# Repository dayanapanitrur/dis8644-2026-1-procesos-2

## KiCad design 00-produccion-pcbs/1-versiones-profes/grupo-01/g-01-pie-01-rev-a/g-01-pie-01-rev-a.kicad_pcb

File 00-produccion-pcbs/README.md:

# produccion-pcbs

jornada maratónica sábado 06 junio 2026

equipo docente toma todos los proyectos de kicad entregados el día anterior, de proyecto-02, y con eso edita, revisa, y envía a producción.

hay 6 grupos de trabajo con una temática en particular, cada grupo realizó 2 esquemáticos con sus respectivas placas, en varias versiones que subieron a la carpeta 00-proyecto-02.

a continuación los apuntes de las distintas revisiones hechas de estos proyectos, para prepararlos para su producción física.

en este repo creamos 3 carpetas:

- 0-versiones-estudiantes: archivos de kicad con las versiones más recientes de proyectos de estudiantes
- 1-versiones-profes: archivos de kicad con las versiones revisadas y realizadas por equipo docentes
- 2-archivos-produccion: gerbers de producción, etiquetados como revA.

## grupo-01: piezos

- benjaminalvarez21
- Anaysval
- chknngttts
- ryukivol
- nicolasvaldesgreve

### g-01-pie-01-rev-a

- cambiamos tamaño r15
- cambiamos conector de entrada
- cambiamos nomenclatura de "100 u" a "100u"
- cambiamos huella de transistor Q1, porque era la equivocada

### g-01-pie-02-rev-a

- no fue enviado a producción porque no tenemos garantía de que funcionara según lo visto en protoboard.

## grupo-02: secuenciadores

- isidoraalvarez
- tomascatri
- dayanapanitrur
- Estrabismx
- angel-udp

### g-02-sec-01-rev-a

en esquemático:

- agregamos resistor de clock in a ground, para pulldown.
- agregamos resistor entre 4040 Q0 patita 9 y salida
- agregamos resistor a cada salida de jack switch.
- cambiamos huellas de transistores a versión inline_wide para que tengan más espacio
- agregados mounting hole faltantes

en pcb:

- actualizamos conectores jack a la huella de la biblioteca, para poder rutear bien los nuevos resistores y no perdernos.

### g-02-sec-02-rev-a

en esquemático:

- agregamos también resistores de protección en entradas y salidas.
- agregados mounting hole faltantes

en pcb:

- actualizamos conectores jack a la huella de la biblioteca, para poder rutear bien los nuevos resistores y no perdernos.

## grupo-03: osciladores 1

- vanessagarciaM
- antoloch
- ccarlabelenn
- arielorozco024
- Narelyriquelme

## grupo-04: osciladores 2

- antokiaraa
- santiagocifuvelez
- paulafuentesm
- kristelagj
- catalinaoyanedel
- yairaruiz

## grupo-05: filtros

- antoniaamc
- Catabalboa
- sebastianguevaralarotta
- CatalinaJeria
- Luisaatoro9

### g-05-fil-01-rev-a

- error grave en la nomenclatura de los proyectos: el 01 en su README dicen que es el activo, pero en Kicad es el pasivo
- cambiamos C1 por condensador no polarizado
- conectamos patita del medio de potenciómetro
- confusión en los tamaños de los condensadores C4 y C5
- los tamaños de las pistas usados no fueron los indicados en clases ni en estandarización
- faltó el paso de agregar tierra a la placa, no está hecho

### g-05-fil-02-rev-a

- error grave en la nomenclatura de los proyectos: el 01 en su README dicen que es el activo, pero en Kicad es el pasivo
- no fue enviado a producción, ya que no funcionó en protoboard

## grupo-06: percusiones

- terroiblea
- martinaechavarria-stack
- Nicolas-Miranda1312
- paredesvania
- Coff4

### g-06-perc-01-rev-a

- agregamos jack de entrada de audio que reemplace la oscilación de entrada
- agregamos ground a los integrados que no están siendo usados

### g-06-perc-02-rev-a

- agregamos el detalle de las entradas de las compuertas lógicas no usadas, fueron conectadas a tierra, para definir sus estados
- C7 estaba en el esquemático pero no en la placa, tuvimos que agregarlo
- C4 le faltaba una conexión en la PCB, la agregamos

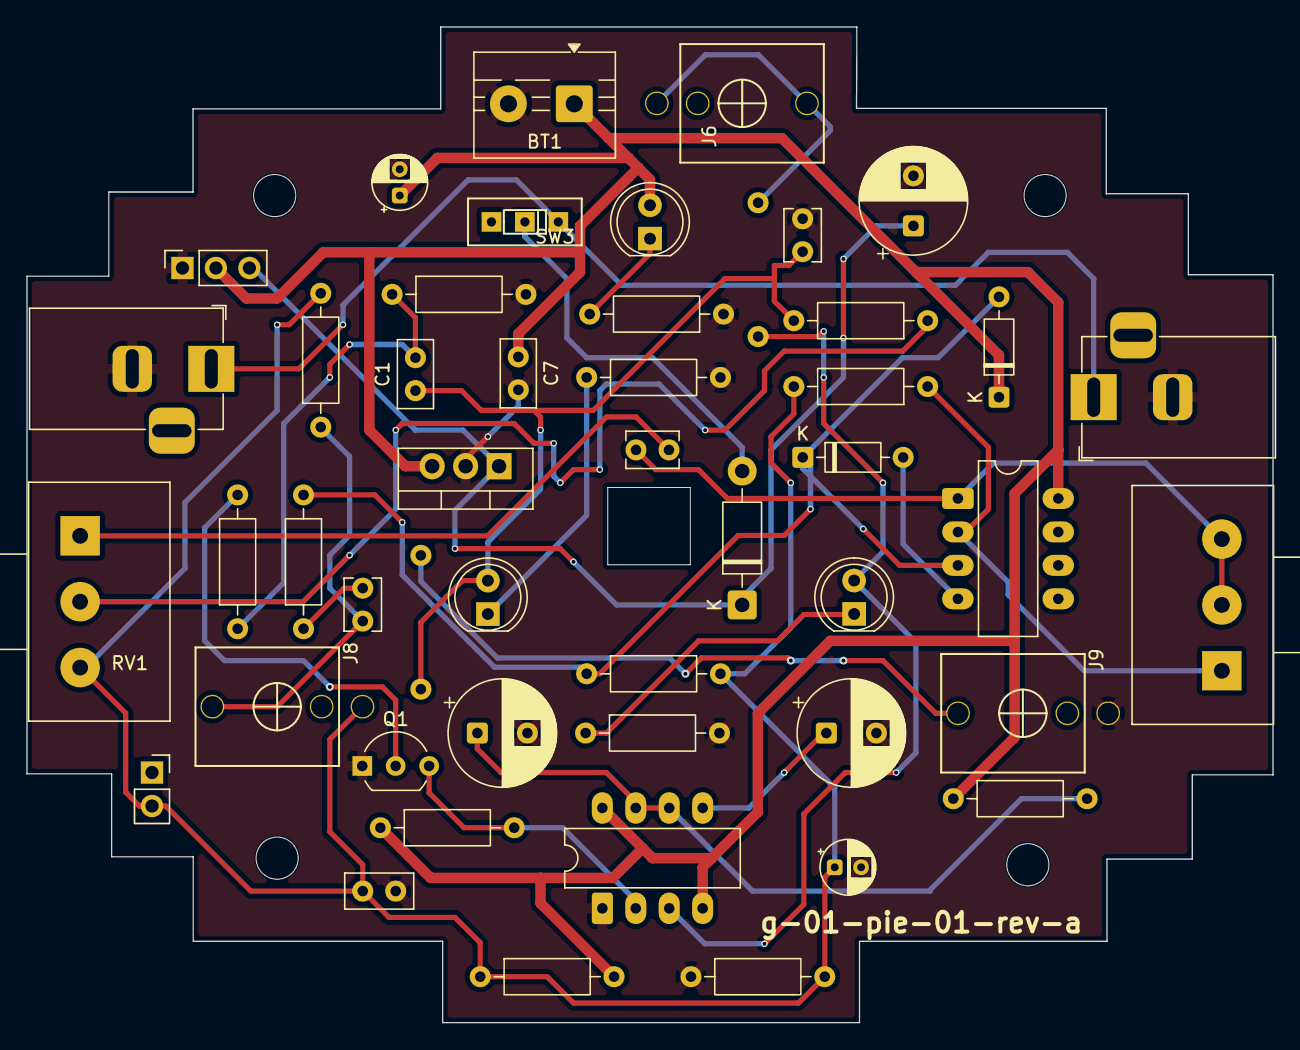
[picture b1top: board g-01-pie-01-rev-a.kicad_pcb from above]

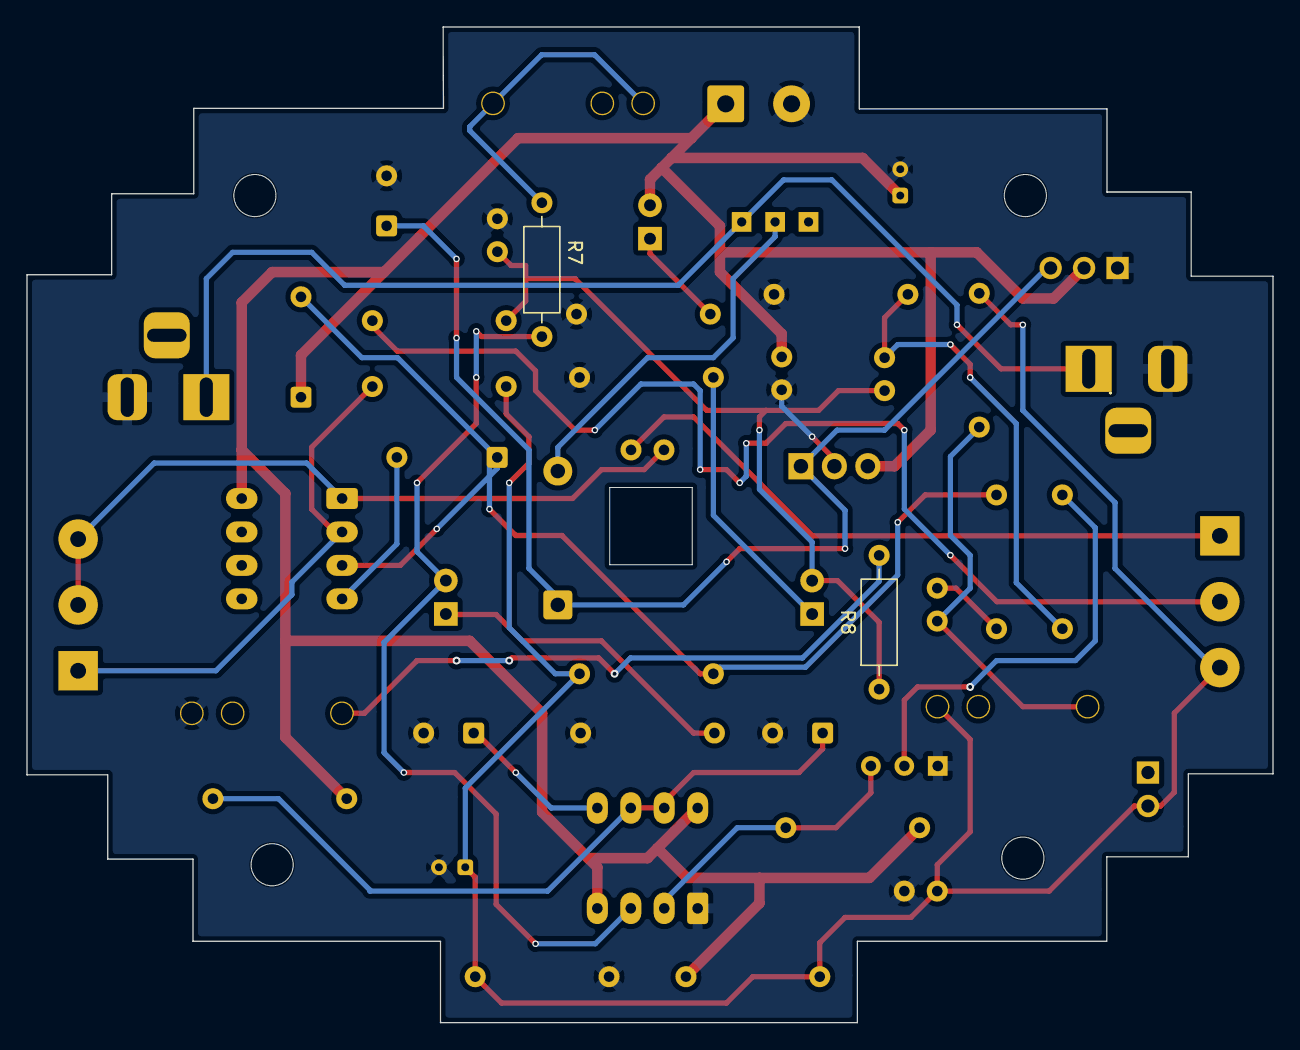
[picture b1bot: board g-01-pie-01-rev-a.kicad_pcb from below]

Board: 2 copper layers, 94.6 x 75.6 mm, 52 parts (2 on the bottom side), 26 nets.

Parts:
BT1: 5v; TerminalBlock_MaiXu_MX126-5.0-02P_1x02_P5.00mm
C1, C7, C10: 100n; C_Disc_D5.0mm_W2.5mm_P2.50mm
C2, C3, C5: 100u; CP_Radial_D8.0mm_P3.80mm
C6, C11: 10u; CP_Radial_D4.0mm_P2.00mm
C9: 1u; C_Disc_D3.8mm_W2.6mm_P2.50mm
C12: 4n7; C_Disc_D3.8mm_W2.6mm_P2.50mm
C13: 10n; C_Disc_D3.8mm_W2.6mm_P2.50mm
D1, D2, D8: LED; LED_D5.0mm
D5: 1N4007; D_DO-41_SOD81_P10.16mm_Horizontal
D6, D7: BAT85; D_DO-35_SOD27_P7.62mm_Horizontal
H1, H2, H3, H4: MountingHole; MountingHole_3.2mm_M3
J2: Conn_01x02_Pin; PinSocket_1x02_P2.54mm_Vertical
J4, J5: Barrel_Jack_Switch; BarrelJack_Horizontal
J6, J8, J9: AudioJack2_SwitchT; PJ301M-12
J7: Conn_01x03_Pin; PinSocket_1x03_P2.54mm_Vertical
Q1: 2N2222; TO-92_Inline_Wide
R1, R3, R6, R7, R8, R11: 1k; R_Axial_DIN0207_L6.3mm_D2.5mm_P10.16mm_Horizontal
R2, R16, R17: 100k; R_Axial_DIN0207_L6.3mm_D2.5mm_P10.16mm_Horizontal
R4, R5: 10k; R_Axial_DIN0207_L6.3mm_D2.5mm_P10.16mm_Horizontal
R12: 47; R_Axial_DIN0207_L6.3mm_D2.5mm_P10.16mm_Horizontal
R13: 2k; R_Axial_DIN0207_L6.3mm_D2.5mm_P10.16mm_Horizontal
R14: 220; R_Axial_DIN0207_L6.3mm_D2.5mm_P10.16mm_Horizontal
R15: 2M; R_Axial_DIN0207_L6.3mm_D2.5mm_P10.16mm_Horizontal
R18: 100; R_Axial_DIN0207_L6.3mm_D2.5mm_P10.16mm_Horizontal
RV1: B10k; Potentiometer_Alps_RK163_Single_Horizontal
RV2: B500k; Potentiometer_Alps_RK163_Single_Horizontal
SW3: SW_SPDT; spdt_ssd12d00g3
U1: NE555P; CERDIP-8_W7.62mm_SideBrazed_LongPads
U3: L7805; TO-220-3_Vertical
U4: TL072; CERDIP-8_W7.62mm_SideBrazed_LongPads

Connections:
+5V: BT1.1 (+), C6.1, C7.1, D6.1 (K), D8.2 (A), J7.2, R4.1, R5.1, R16.2, U1.4 (~RST), U1.8 (VCC), U3.3 (OUT), U4.8 (V+)
+12V: C5.1, D5.1 (K), J7.3, U3.1 (IN)
GND: BT1.2 (-), C2.2, C3.2, C5.2, C6.2, C7.2, C10.2, C11.2, C12.2, J4.2, J5.2, J7.1, J9.1, Q1.1 (E), R1.2, R2.2, R6.2, R11.1, R17.1, U1.1 (GND), U3.2 (GND)
unnamed: C1.2, R2.1, R3.1
unnamed: C9.1, J8.3, R15.1
unnamed: C9.2, R14.1
unnamed: C13.1, RV2.2, RV2.3, U4.1
unnamed: C13.2, RV1.1
unnamed: C1.1, C12.1, D1.2 (A), R8.1, R18.2
unnamed: D1.1 (K), R1.1
unnamed: D2.2 (A), R7.1, U1.3 (OUT)
unnamed: D2.1 (K), R6.1
unnamed: D5.2 (A), SW3.2 (B)
unnamed: D6.2 (A), D7.1 (K), R13.1, R14.2, U4.3 (+)
unnamed: D7.2 (A), U4.4 (V-)
unnamed: D8.1 (K), R11.2
unnamed: J6.1, J6.2, R7.2
unnamed: J9.3, R8.2
unnamed: Q1.2 (B), R3.2
unnamed: Q1.3 (C), R4.2, U1.2 (TRIG)
unnamed: R18.1, RV1.2
unnamed: J4.1, J5.1, SW3.1 (A)
unnamed: C3.1, U1.5 (CONT)
unnamed: C2.1, R5.2, U1.6 (THRES), U1.7 (DISCH)
unnamed: R12.1, RV2.1, U4.2 (-)
VBUS: C10.1, C11.1, J2.2, J8.1, R12.2, R13.2, R15.2, R16.1, R17.2, RV1.3

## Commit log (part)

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2026-05-05 agrego imagenes instalación kicad
2026-05-05 agrego pcb kicad
2026-05-05 arreglo en redacción
2026-05-12 Update README title with additional details
2026-05-12 agrego imagenes
2026-05-12 Add class link to README for sesion-08a
2026-05-12 Update README.md with session date and new section
2026-05-12 agregar mas apuntes
2026-05-12 agregar mas texto sobre semanas 08a y 09b
2026-05-13 agrego apuntes sin terminar
2026-05-13 agrego un poco del encargo
    me falta aún pero tengo que trabajar para otro ramo, vuelvo en la noche
2026-05-14 agregar
2026-05-14 agrego apuntes finales de kicad
2026-05-14 apuntes
2026-05-14 agrego mencion encargo libro
2026-05-14 agrego apuntes desordenados
2026-05-14 agrego final encargo
2026-05-15 Add component table to README
    Added a table listing various components, their KiCad footprints, and typical uses.
2026-05-17 Add 'G' command for grabbing components
2026-05-17 traspaso apuntes
2026-05-18 Rename Captura de pantalla 2026-05-18 182952.png to encargo01.png
2026-05-18 Rename Captura de pantalla 2026-05-18 182943.png to encargo02.png
2026-05-18 15 mayo
2026-05-18 Refactor README.md for clarity and organization
2026-05-19 Update README with date and greeting
    Added date and greeting to README.
2026-05-19 En edicion
    Added sections for Encargo 1 and Encargo 2 with related content.
2026-05-19 no-cambio-tamano-voy-denuevo
2026-05-19 README.md
2026-05-19 apuntes agregados
2026-05-22 En edicion
2026-05-22 agrego ss
2026-05-22 Update README format for date section
2026-05-22 Revise README for session 10a with new content
    Updated README.md to reflect new session details and content changes.
2026-05-22 sesion-in-correcta
2026-05-24 agrego nombres y github integrantes
2026-05-25 Add 'receso' to sesion-09a README
2026-05-26 Update README with modular grid and resource link
    Added information about modular grid and resources for low and high-pass filters.
2026-05-26 añadido proyecto ejemplo
2026-05-27 imagenes-sin-musica
2026-06-02 Add details about chips and oscillator options
2026-06-02 Update README with schematics and materials note
    Added schematics images and note about missing materials.
2026-06-02 Add date header to README for sesion-12a
2026-06-03 cambiar-carpeta
2026-06-03 agregar carpeta
2026-06-03 agregar grupo-02
2026-06-04 agrego info 01
2026-06-04 arreglo
2026-06-05 Create ssss
2026-06-05 Revise project overview and collaboration section
    Updated project description and collaboration details in README.
2026-06-05 Rename secuenciador-02-v02-esquematico.PNG to secuenciador-02-v02-esquematico.png
2026-06-06 agrego versión final modulo 01 piezo
2026-06-06 agregar grupo-05
2026-06-06 corregido g01
2026-06-09 entrega-2-mini-texto
2026-06-09 Update README with project delivery information
    Added project delivery note to README.
2026-06-10 imagenes-1
2026-06-14 sesion 12b
2026-06-14 Update section title for component manipulation
2026-06-14 Update README with session 11b details
    Added details about the session's activities, including issues faced with the oscillator setup and troubleshooting steps taken.
2026-06-15 lectura y apuntes
2026-06-15 Rename 17029304828162891.jpg to idea-03.jpg
2026-06-18 Expand README with insights from chapters 5 and 6
    Added reflections on chapters 5 and 6 from Pomelo, including personal experiences and insights on creation and destruction.
2026-06-18 Rename Captura de pantalla 2026-06-16 080543.png to yoko-ono.png
2026-06-18 agregar imagenes
2026-06-19 falta agregar imagenes
2026-06-19 Update README with project details and materials
2026-06-19 Revise README with project information and visuals
    Updated README.md to include project details, materials list, assembly process, and graphical scores.
2026-06-19 Fix typo in README for Chapter 6 - Cine
    Corrected a phrase for clarity in the README.
2026-06-19 Revise README
    Updated README.md to include additional project details and BOM information.
2026-06-19 tamaño-color
2026-06-24 Update README with class session details
    Added detailed notes about the soldering process and issues encountered during class.
2026-06-28 nombre-raro
2026-06-30 agregar grupo-06
2026-06-30 agregar carpeta imagenes
